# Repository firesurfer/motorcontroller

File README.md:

# motorcontroller
Motorcontroller for two DC motors up to 30A at 12V. 

Using the following external eagle libs:
https://github.com/chiengineer/Eagle-Libraries/blob/master/Vendors/st-microelectronics.lbr

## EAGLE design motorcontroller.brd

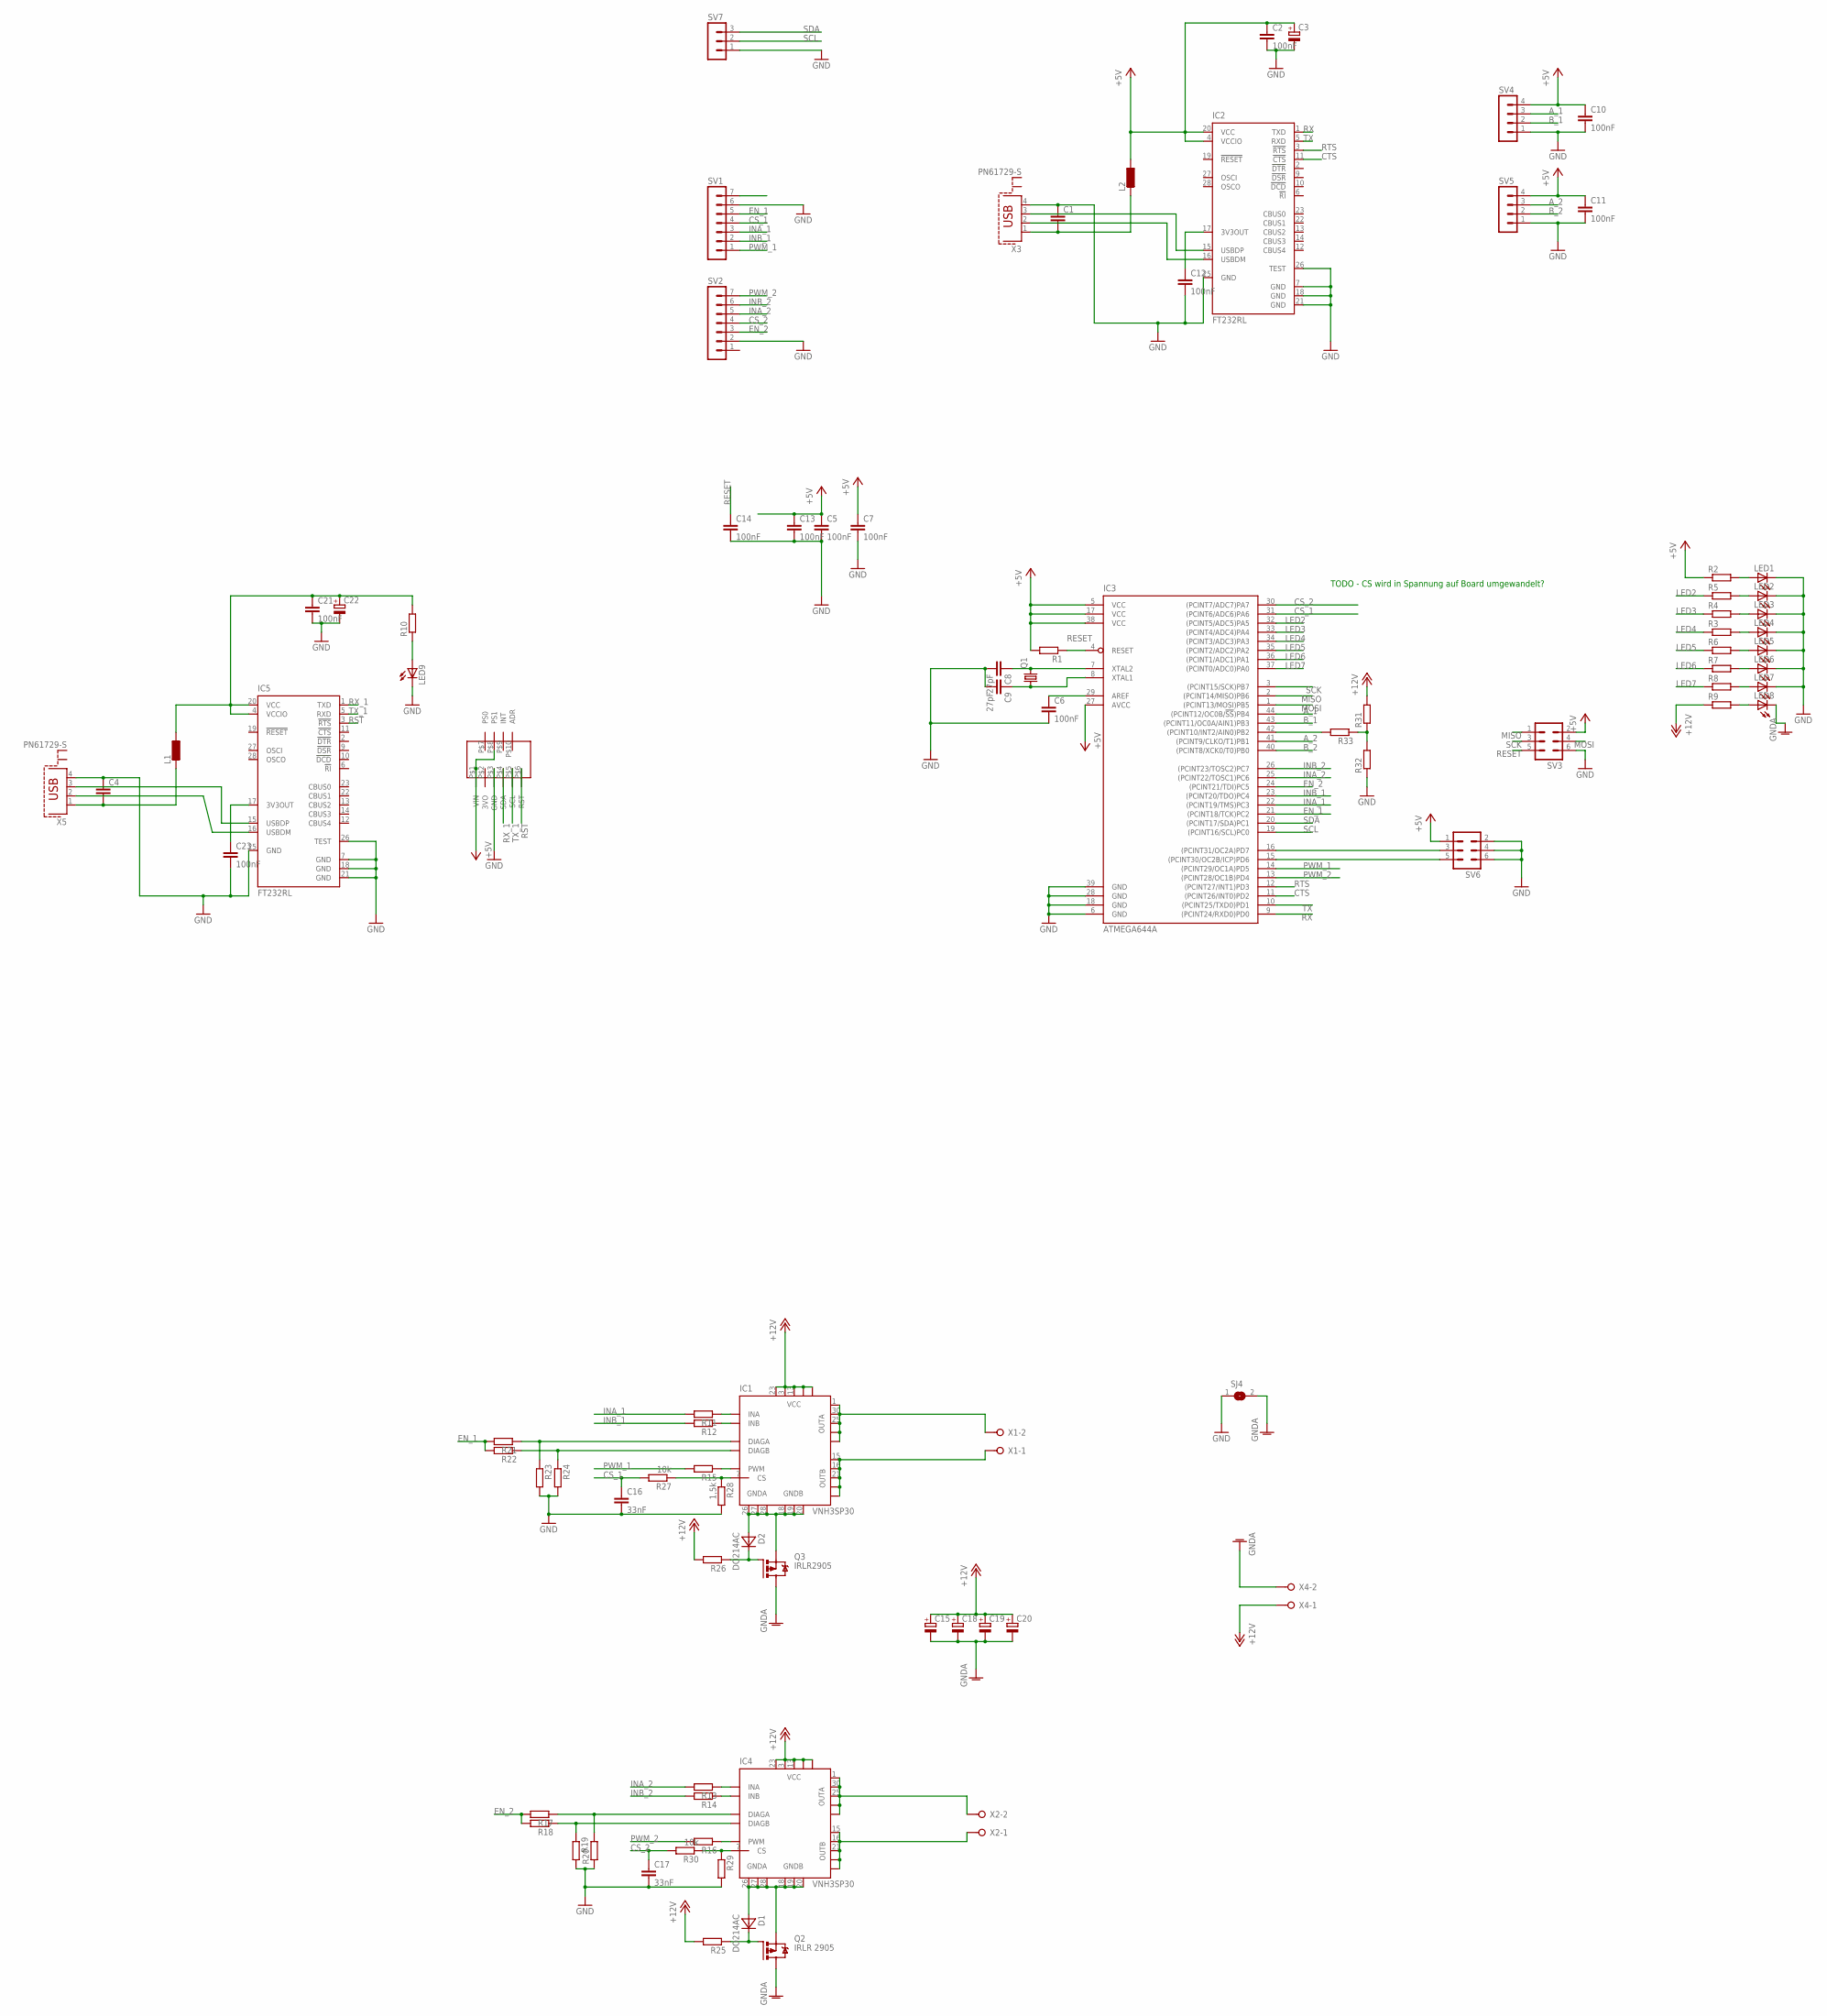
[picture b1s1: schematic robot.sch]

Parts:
C1, C4: C-EUC0805; C0805
C2, C5, C6, C7, C10, C11, C12, C13, C14, C21, C23: 100nF; C0805
C3, C15, C18, C19, C20, C22: CPOL-EU153CLV-0810; 153CLV-0810
C8, C9: 27pF; C0805
C16, C17: 33nF; C0805
D1, D2: DO214AC; SMA
IC1, IC4: VNH3SP30; MULTIPOWERSO-30
IC2, IC5: FT232RL; SSOP28
IC3: ATMEGA644A; TQFP44
L1, L2: LL4532C; L4532M
LED1, LED2, LED3, LED4, LED5, LED6, LED7, LED8, LED9: LEDCHIPLED_0805; CHIPLED_0805
Q1: CRYSTALHC49UP; HC49UP
Q2: IRLR 2905; D-PAK_TO252AA
Q3: IRLR2905; D-PAK_TO252AA
R1, R2, R3, R4, R5, R6, R7, R8, R9, R10, R11, R12, R13, R14, R15, R16, R17, R18, R19, R20, R21, R22, R23, R24, R25, R26, R29, R31, R32, R33: R-EU_M0805; M0805
R27, R30: 10k; M0805
R28: 1,5k; M0805
SJ4: SJ
SV1, SV2: MA07-1
SV3, SV6: ML6
SV4, SV5: MA04-1
SV7: MA03-1
U$1: BNO055; BNO055_ADA
X1, X2, X4: W237-02P; W237-132
X3, X5: PN61729-S

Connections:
+5V: C2.1, C3.+, C5.1, C7.1, C10.1, C11.1, C13.1, IC2.4 (VCCIO), IC2.20 (VCC), IC3.5 (VCC), IC3.17 (VCC), IC3.27 (AVCC), IC3.38 (VCC), L2.1, R1.2, R2.1, SV3.2, SV4.4, SV5.4, SV6.1, U$1.P$1 (VIN), U$1.P$8 (PS1)
+12V: C15.+, C18.+, C19.+, C20.+, IC1.3 (VCC), IC1.13 (VCC), IC1.23 (VCC), IC1.VCC, IC1.VCC@1 (VCC), IC4.3 (VCC), IC4.13 (VCC), IC4.23 (VCC), IC4.VCC, IC4.VCC@1 (VCC), R9.1, R25.2, R26.2, R31.2, X4.1
A_1: IC3.44 ((PCINT12/OC0B/!SS!)PB4), SV4.3
A_2: IC3.41 ((PCINT9/CLKO/T1)PB1), SV5.3
B_1: IC3.43 ((PCINT11/OC0A/AIN1)PB3), SV4.2
B_2: IC3.40 ((PCINT8/XCK0/T0)PB0), SV5.2
CS_1: C16.1, IC3.31 ((PCINT6/ADC6)PA6), R27.2, SV1.4
CS_2: C17.1, IC3.30 ((PCINT7/ADC7)PA7), R30.2, SV2.4
CTS: IC2.11 (!CTS), IC3.11 ((PCINT26/INT0)PD2)
EN_1: IC3.21 ((PCINT18/TCK)PC2), R21.2, R22.2, SV1.5
EN_2: IC3.24 ((PCINT21/TDI)PC5), R17.2, R18.2, SV2.3
GND: C1.1, C2.2, C3.-, C4.1, C5.2, C6.2, C7.2, C8.2, C9.2, C10.2, C11.2, C12.2, C13.2, C14.2, C16.2, C17.2, C21.2, C22.-, C23.2, IC2.7 (GND), IC2.18 (GND), IC2.21 (GND), IC2.25 (GND), IC2.26 (TEST), IC3.6 (GND), IC3.18 (GND), IC3.28 (GND), IC3.39 (GND), IC5.7 (GND), IC5.18 (GND), IC5.21 (GND), IC5.25 (GND), IC5.26 (TEST), LED1.C, LED2.C, LED3.C, LED4.C, LED5.C, LED6.C, LED7.C, LED9.C, R19.2, R20.1, R23.2, R24.2, R28.2, R29.2, R32.1, SJ4.1, SV1.6, SV2.2, SV3.6, SV4.1, SV5.1, SV6.2, SV6.4, SV6.6, SV7.1, U$1.P$3 (GND), X3.4, X5.4
GNDA: C15.-, C18.-, C19.-, C20.-, LED8.C, Q2.4 (D), Q3.4 (D), SJ4.2, X4.2
INA_1: IC3.22 ((PCINT19/TMS)PC3), R11.2, SV1.3
INA_2: IC3.25 ((PCINT22/TOSC1)PC6), R13.2, SV2.5
INB_1: IC3.23 ((PCINT20/TDO)PC4), R12.2, SV1.2
INB_2: IC3.26 ((PCINT23/TOSC2)PC7), R14.2, SV2.6
LED2: IC3.32 ((PCINT5/ADC5)PA5), R5.1
LED3: IC3.33 ((PCINT4/ADC4)PA4), R4.1
LED4: IC3.34 ((PCINT3/ADC3)PA3), R3.1
LED5: IC3.35 ((PCINT2/ADC2)PA2), R6.1
LED6: IC3.36 ((PCINT1/ADC1)PA1), R7.1
LED7: IC3.37 ((PCINT0/ADC0)PA0), R8.1
MISO: IC3.2 ((PCINT14/MISO)PB6), SV3.1
MOSI: IC3.1 ((PCINT13/MOSI)PB5), SV3.4
unnamed: LED1.A, R2.2
unnamed: IC2.16 (USBDM), X3.2
unnamed: IC2.15 (USBDP), X3.3
unnamed: LED4.A, R3.2
unnamed: LED3.A, R4.2
unnamed: C8.1, IC3.7 (XTAL2), Q1.2
unnamed: C9.1, IC3.8 (XTAL1), Q1.1
unnamed: LED2.A, R5.2
unnamed: C6.1, IC3.29 (AREF)
unnamed: LED5.A, R6.2
unnamed: LED6.A, R7.2
unnamed: LED7.A, R8.2
unnamed: C1.2, L2.2, X3.1
unnamed: LED8.A, R9.2
unnamed: LED9.A, R10.1
unnamed: C12.1, IC2.17 (3V3OUT)
unnamed: IC4.5 (INA), R13.1
unnamed: IC5.16 (USBDM), X5.2
unnamed: IC4.11 (INB), R14.1
unnamed: IC4.8 (PWM), R16.1
unnamed: IC1.5 (INA), R11.1
unnamed: IC1.11 (INB), R12.1
unnamed: IC1.8 (PWM), R15.1
unnamed: IC4.6 (DIAGA), R17.1, R20.2
unnamed: IC4.10 (DIAGB), R18.1, R19.1
unnamed: D2.A, IC1.18 (GNDB), IC1.19 (GNDB), IC1.20 (GNDB), IC1.26 (GNDA), IC1.27 (GNDA), IC1.28 (GNDA), Q3.3 (S)
unnamed: IC1.6 (DIAGA), R21.1, R23.1
unnamed: IC1.10 (DIAGB), R22.1, R24.1
unnamed: D1.A, IC4.18 (GNDB), IC4.19 (GNDB), IC4.20 (GNDB), IC4.26 (GNDA), IC4.27 (GNDA), IC4.28 (GNDA), Q2.3 (S)
unnamed: D1.C, Q2.1 (G), R25.1
unnamed: D2.C, Q3.1 (G), R26.1
unnamed: IC4.1 (OUTA), IC4.25 (OUTA), IC4.30 (OUTA), IC4.OUTA, IC4.OUTA@1 (OUTA), X2.2
unnamed: IC4.15 (OUTB), IC4.16 (OUTB), IC4.21 (OUTB), IC4.OUTB, IC4.OUTB@1 (OUTB), X2.1
unnamed: IC1.15 (OUTB), IC1.16 (OUTB), IC1.21 (OUTB), IC1.OUTB, IC1.OUTB@1 (OUTB), X1.1
unnamed: IC1.1 (OUTA), IC1.25 (OUTA), IC1.30 (OUTA), IC1.OUTA, IC1.OUTA@1 (OUTA), X1.2
unnamed: IC1.7 (CS), R27.1, R28.1
unnamed: IC4.7 (CS), R29.1, R30.1
unnamed: IC5.15 (USBDP), X5.3
unnamed: C4.2, L1.2, X5.1
unnamed: C23.1, IC5.17 (3V3OUT)
unnamed: C21.1, C22.+, IC5.4 (VCCIO), IC5.20 (VCC), L1.1, R10.2
unnamed: IC3.16 ((PCINT31/OC2A)PD7), SV6.3
unnamed: IC3.15 ((PCINT30/OC2B/ICP)PD6), SV6.5
unnamed: R31.1, R32.2, R33.1
unnamed: IC3.42 ((PCINT10/INT2/AIN0)PB2), R33.2
PWM_1: IC3.14 ((PCINT29/OC1A)PD5), R15.2, SV1.1
PWM_2: IC3.13 ((PCINT28/OC1B)PD4), R16.2, SV2.7
RESET: C14.1, IC3.4 (RESET), R1.1, SV3.5
RST: IC5.3 (!RTS), U$1.P$6 (RST)
RTS: IC2.3 (!RTS), IC3.12 ((PCINT27/INT1)PD3)
RX: IC2.1 (TXD), IC3.9 ((PCINT24/RXD0)PD0)
RX_1: IC5.1 (TXD), U$1.P$4 (SDA)
SCK: IC3.3 ((PCINT15/SCK)PB7), SV3.3
SCL: IC3.19 ((PCINT16/SCL)PC0), SV7.2
SDA: IC3.20 ((PCINT17/SDA)PC1), SV7.3
TX: IC2.5 (RXD), IC3.10 ((PCINT25/TXD0)PD1)
TX_1: IC5.5 (RXD), U$1.P$5 (SCL)

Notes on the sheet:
TODO - CS wird in Spannung auf Board umgewandelt?

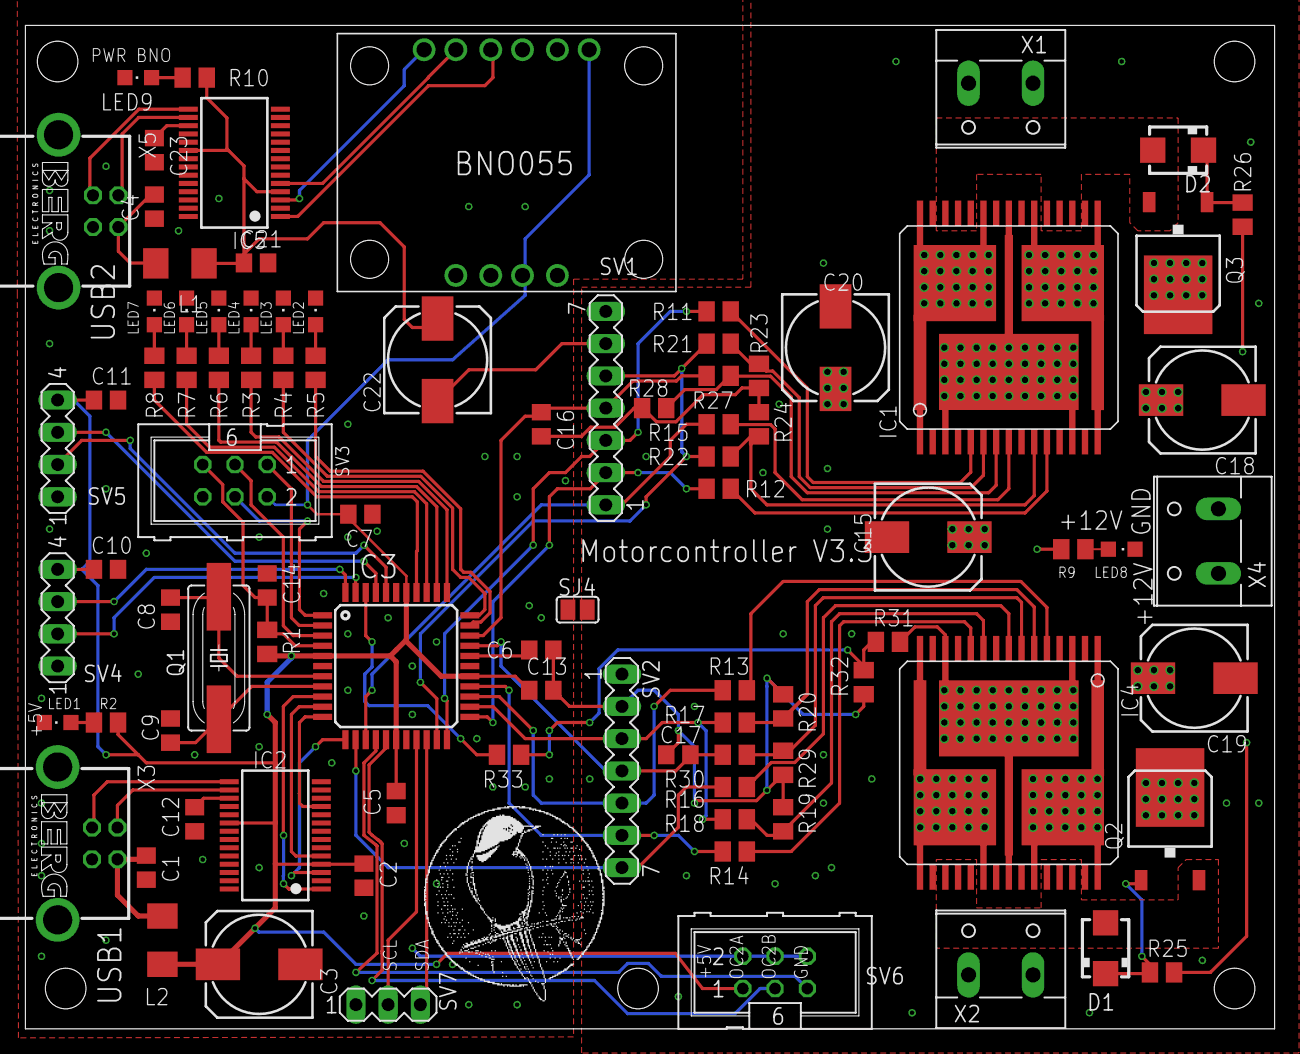
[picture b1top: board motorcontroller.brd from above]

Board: 2 copper layers, 98.4 x 79.0 mm, 91 parts (0 on the bottom side), 82 nets.

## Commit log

2018-02-02 init
2018-02-02 renamed eagle files
